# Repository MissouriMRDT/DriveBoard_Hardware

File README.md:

# DriveBoard_Hardware
Hardware files for Drive Board

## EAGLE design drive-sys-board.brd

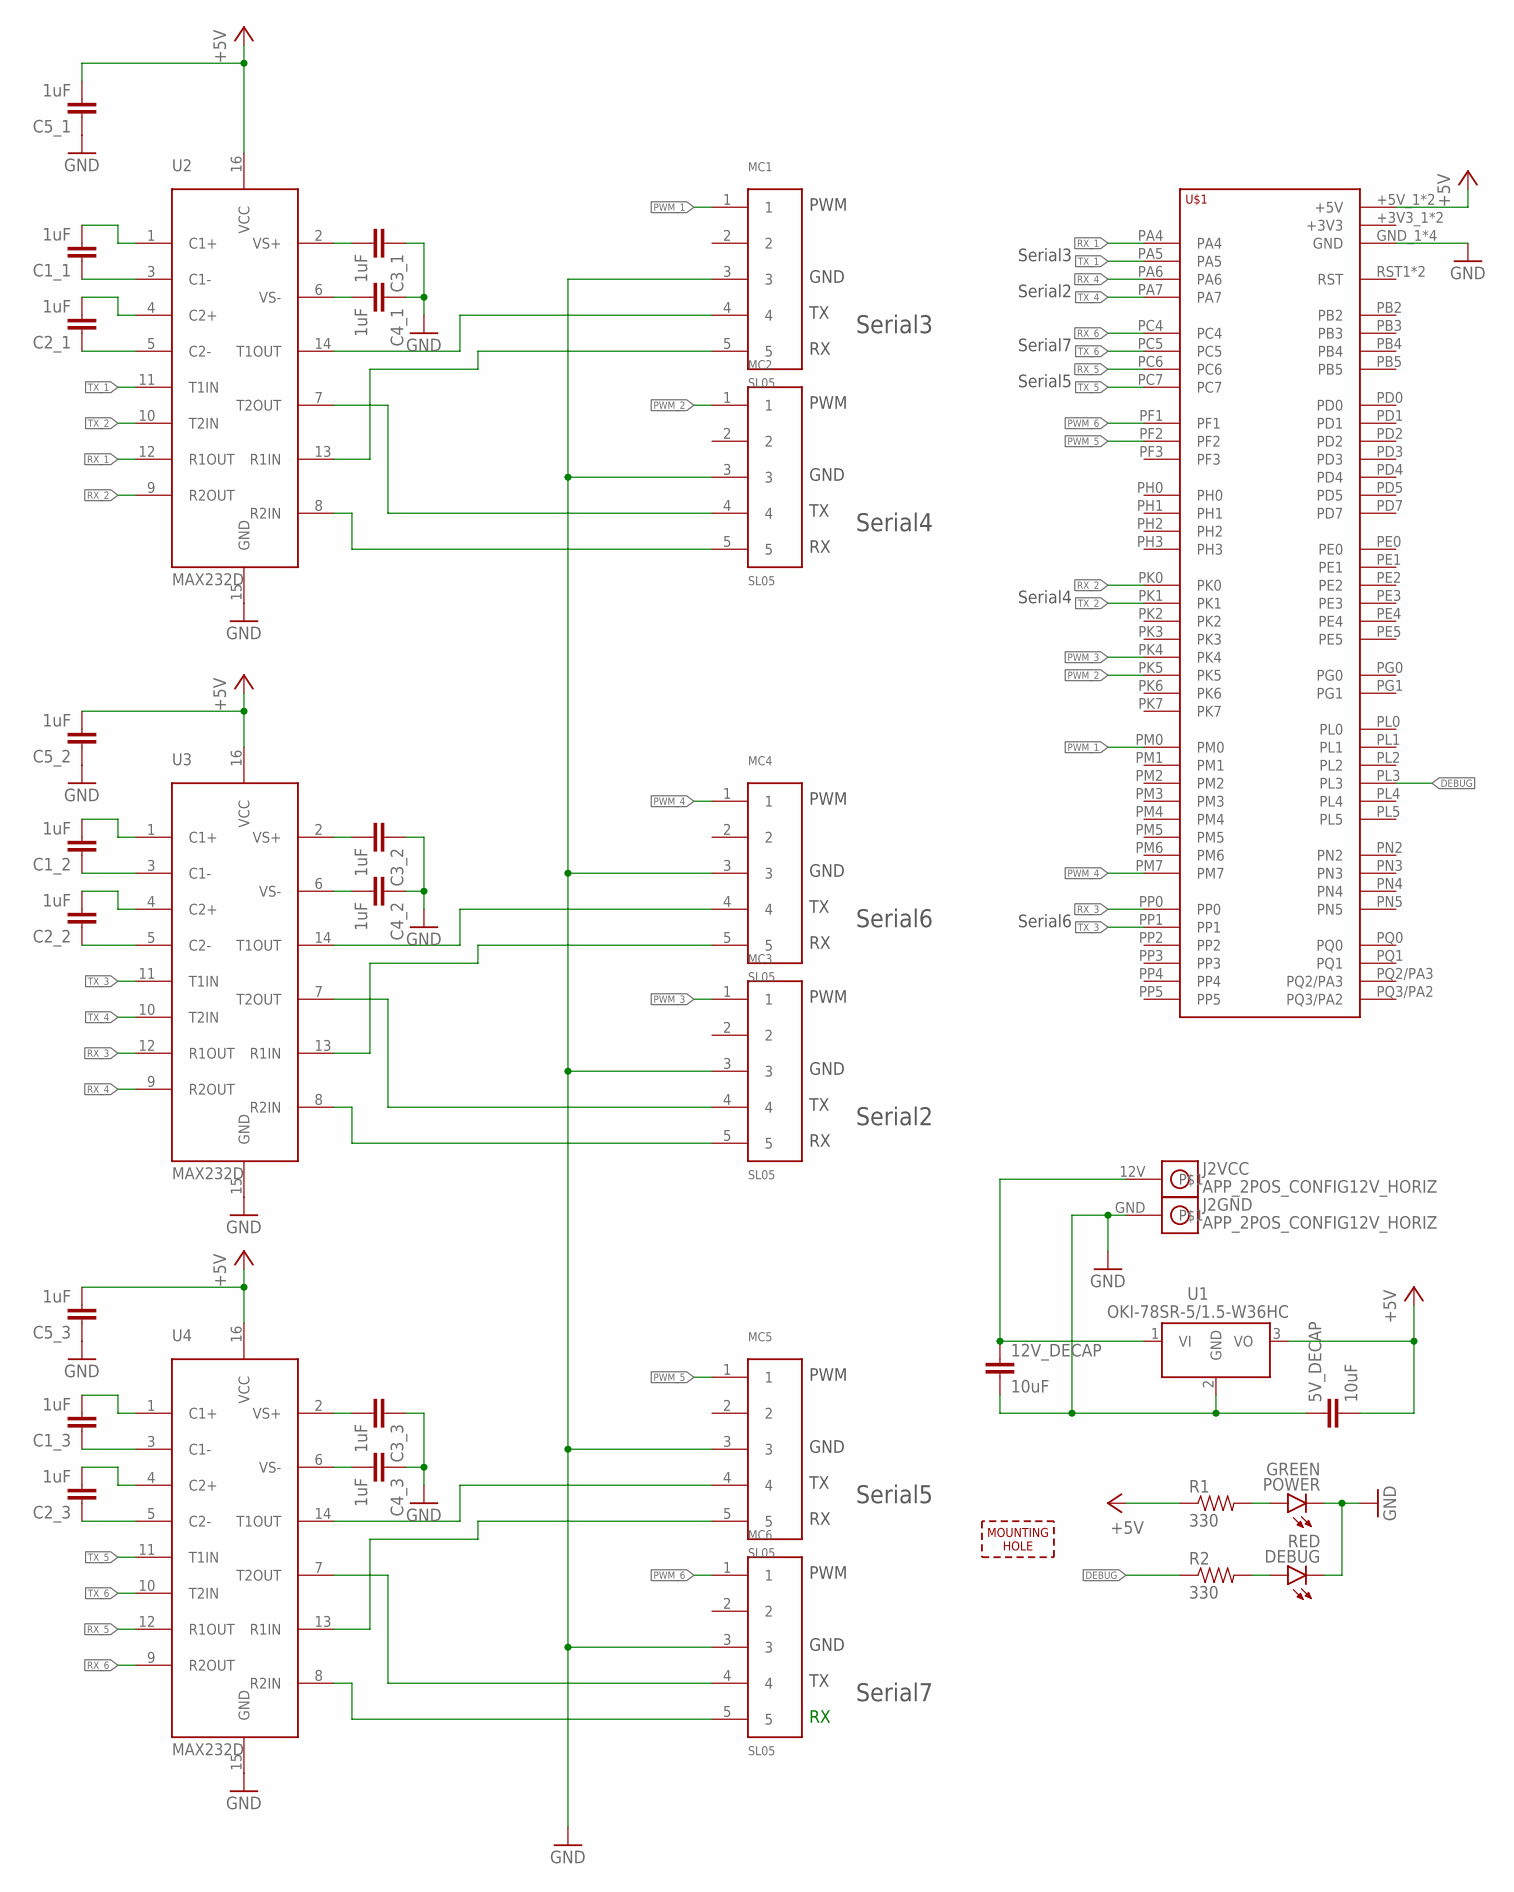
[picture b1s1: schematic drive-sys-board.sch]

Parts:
5V_DECAP, 12V_DECAP: 10uF; 0805
C1_1, C1_2, C1_3, C2_1, C2_2, C2_3, C3_1, C3_2, C3_3, C4_1, C4_2, C4_3, C5_1, C5_2, C5_3: 1uF; 0805
DEBUG: RED; LED-1206
H2: MOUNTING_HOLE#6; #6_SCREW
J2: APP_2POS_CONFIG12V_HORIZ; APP45_12V_HORIZ_CONFIG
MC1, MC2, MC3, MC4, MC5, MC6: SL05; MOLEX_SL_05_TH
POWER: GREEN; LED-1206
R1, R2: 330; 0805
U1: OKI-78SR-5/1.5-W36HC; OKI-78SR_HORIZ
U2, U3, U4: MAX232D; SOIC16
U$1: TIVA-1294; TIVA-C-CONNECTED

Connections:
+5V: 5V_DECAP.2, C5_1.2, C5_2.2, C5_3.2, R1.1, U1.3 (VO), U2.16 (VCC), U3.16 (VCC), U4.16 (VCC), U$1.+5V_1 (+5V), U$1.+5V_2 (+5V)
DEBUG: R2.1, U$1.PL3
GND: 5V_DECAP.1, 12V_DECAP.2, C3_1.1, C3_2.1, C3_3.1, C4_1.1, C4_2.1, C4_3.1, C5_1.1, C5_2.1, C5_3.1, DEBUG.C, J2.GND, MC1.3, MC2.3, MC3.3, MC4.3, MC5.3, MC6.3, POWER.C, U1.2 (GND), U2.15 (GND), U3.15 (GND), U4.15 (GND), U$1.GND_1 (GND), U$1.GND_2 (GND), U$1.GND_3 (GND), U$1.GND_4 (GND)
unnamed: C1_1.2, U2.1 (C1+)
unnamed: C1_1.1, U2.3 (C1-)
unnamed: 12V_DECAP.1, J2.12V, U1.1 (VI)
unnamed: C2_1.2, U2.4 (C2+)
unnamed: C2_1.1, U2.5 (C2-)
unnamed: C3_1.2, U2.2 (VS+)
unnamed: C4_1.2, U2.6 (VS-)
unnamed: DEBUG.A, R2.2
unnamed: C1_2.2, U3.1 (C1+)
unnamed: C1_2.1, U3.3 (C1-)
unnamed: C2_2.2, U3.4 (C2+)
unnamed: C3_2.2, U3.2 (VS+)
unnamed: C4_2.2, U3.6 (VS-)
unnamed: C2_2.1, U3.5 (C2-)
unnamed: POWER.A, R1.2
unnamed: C1_3.2, U4.1 (C1+)
unnamed: C1_3.1, U4.3 (C1-)
unnamed: C2_3.2, U4.4 (C2+)
unnamed: C3_3.2, U4.2 (VS+)
unnamed: C4_3.2, U4.6 (VS-)
unnamed: C2_3.1, U4.5 (C2-)
unnamed: MC5.4, U4.14 (T1OUT)
unnamed: MC6.5, U4.8 (R2IN)
unnamed: MC6.4, U4.7 (T2OUT)
unnamed: MC5.5, U4.13 (R1IN)
unnamed: MC3.5, U3.8 (R2IN)
unnamed: MC3.4, U3.7 (T2OUT)
unnamed: MC4.4, U3.14 (T1OUT)
unnamed: MC4.5, U3.13 (R1IN)
unnamed: MC2.5, U2.8 (R2IN)
unnamed: MC2.4, U2.7 (T2OUT)
unnamed: MC1.4, U2.14 (T1OUT)
unnamed: MC1.5, U2.13 (R1IN)
PWM_1: MC1.1, U$1.PM0
PWM_2: MC2.1, U$1.PK5
PWM_3: MC3.1, U$1.PK4
PWM_4: MC4.1, U$1.PM7
PWM_5: MC5.1, U$1.PF2
PWM_6: MC6.1, U$1.PF1
RX_1: U2.12 (R1OUT), U$1.PA4
RX_2: U2.9 (R2OUT), U$1.PK0
RX_3: U3.12 (R1OUT), U$1.PP0
RX_4: U3.9 (R2OUT), U$1.PA6
RX_5: U4.12 (R1OUT), U$1.PC6
RX_6: U4.9 (R2OUT), U$1.PC4
TX_1: U2.11 (T1IN), U$1.PA5
TX_2: U2.10 (T2IN), U$1.PK1
TX_3: U3.11 (T1IN), U$1.PP1
TX_4: U3.10 (T2IN), U$1.PA7
TX_5: U4.11 (T1IN), U$1.PC7
TX_6: U4.10 (T2IN), U$1.PC5

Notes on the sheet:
PWM
GND
Serial2
Serial3
Serial7
Serial5
Serial4
Serial6

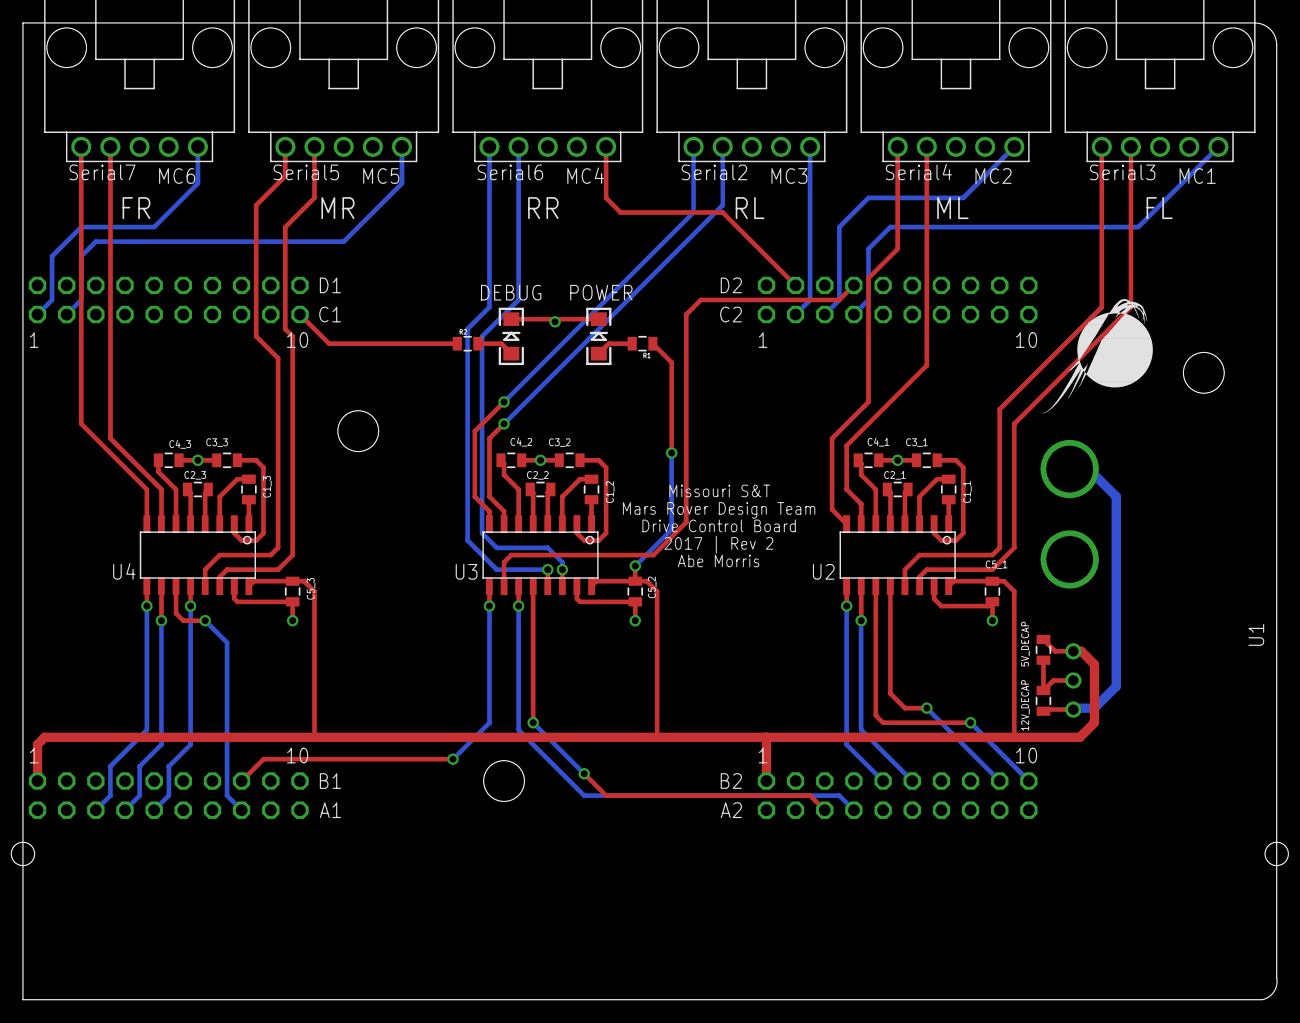
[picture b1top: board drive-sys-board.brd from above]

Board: 2 copper layers, 109.2 x 85.1 mm, 37 parts (0 on the bottom side), 54 nets.

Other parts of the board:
H1, H3: MOUNTING_HOLE#6; #6_SCREW
U$2: MRDT_LOGO

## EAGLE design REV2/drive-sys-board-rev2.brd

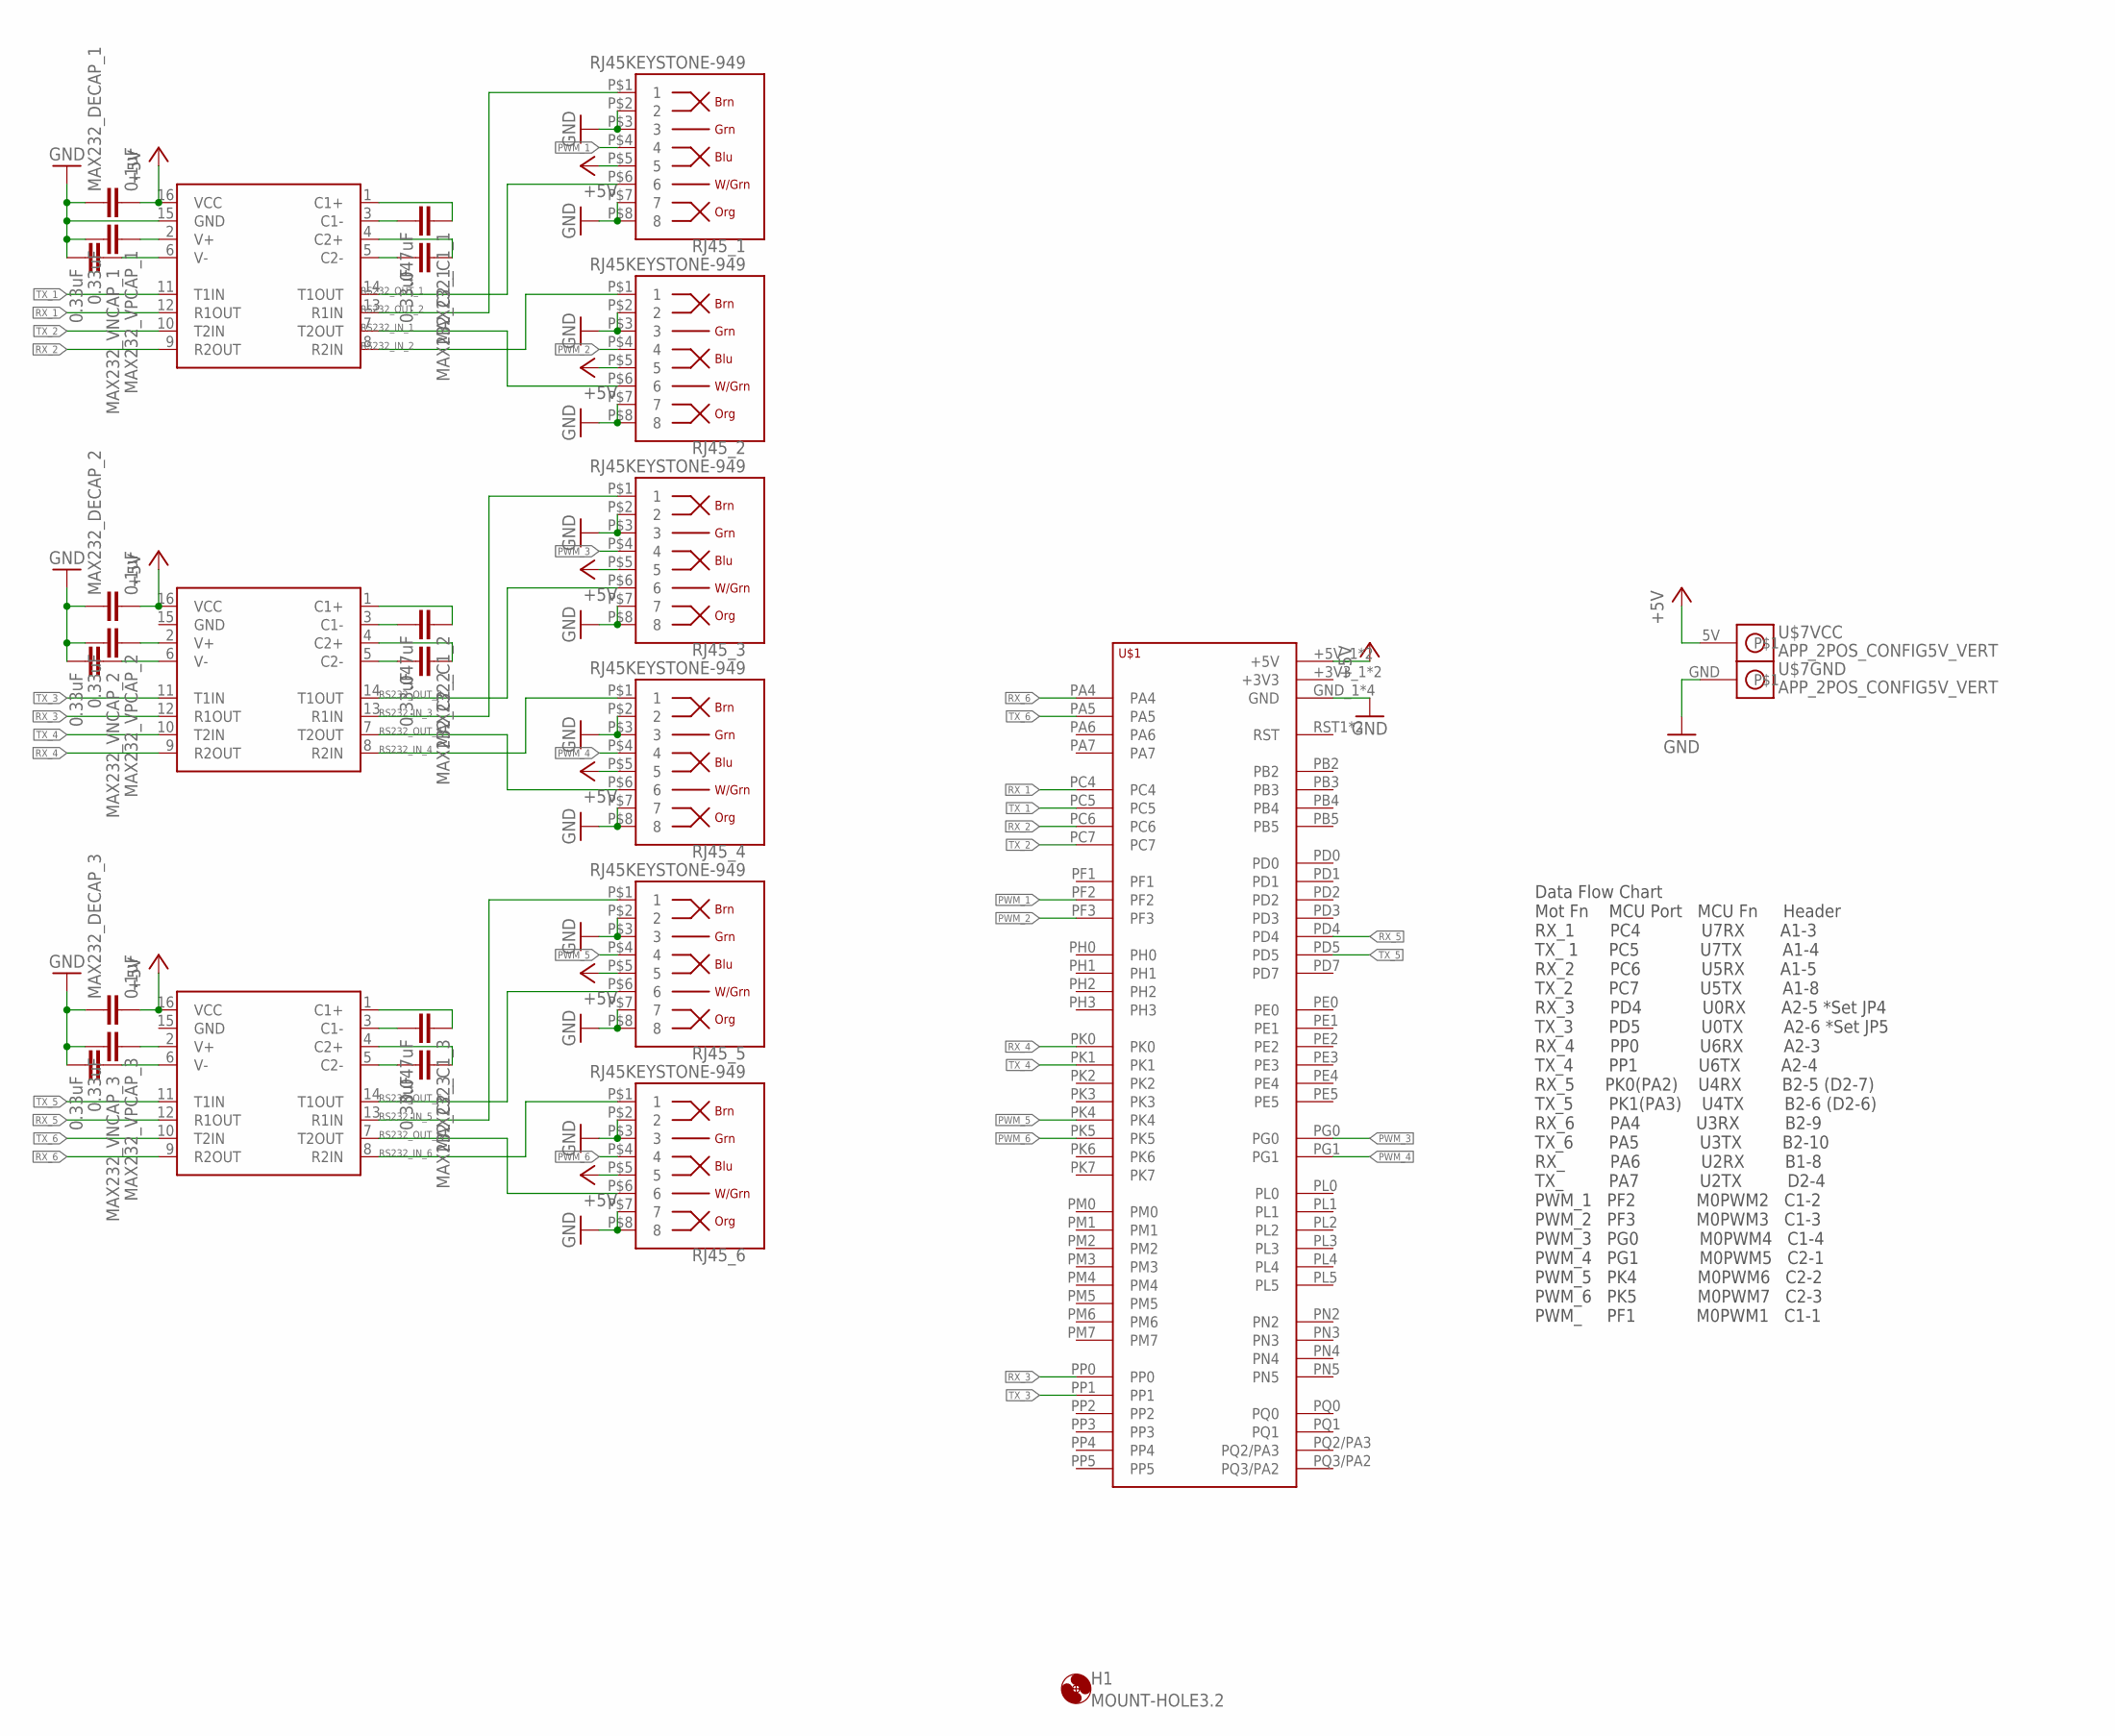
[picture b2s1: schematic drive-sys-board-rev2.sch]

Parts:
H1: MOUNT-HOLE3.2; 3,2
MAX232_1, MAX232_2, MAX232_3: MAX3232SO16; SO16
MAX232_C1_1, MAX232_C1_2: .047uF; 1206
MAX232_C1_3: 0.047uF; 1206
MAX232_C2_1, MAX232_C2_2, MAX232_C2_3, MAX232_VNCAP_1, MAX232_VNCAP_2, MAX232_VNCAP_3, MAX232_VPCAP_1, MAX232_VPCAP_2, MAX232_VPCAP_3: 0.33uF; 1206
MAX232_DECAP_1, MAX232_DECAP_2, MAX232_DECAP_3: 0.1uF; 1206
RJ45_1, RJ45_2, RJ45_3, RJ45_4, RJ45_5, RJ45_6: RJ45KEYSTONE-949; KEYSTONE-949
U$1: TIVA-C-CONNECTED
U$7: APP_2POS_CONFIG5V_VERT; APP45_5V_VERT_CONFIG

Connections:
+5V: MAX232_1.16 (VCC), MAX232_2.16 (VCC), MAX232_3.16 (VCC), MAX232_DECAP_1.2, MAX232_DECAP_2.2, MAX232_DECAP_3.2, RJ45_1.P$5 (5), RJ45_2.P$5 (5), RJ45_3.P$5 (5), RJ45_4.P$5 (5), RJ45_5.P$5 (5), RJ45_6.P$5 (5), U$1.+5V_1 (+5V), U$1.+5V_2 (+5V), U$7.5V
GND: MAX232_1.15 (GND), MAX232_DECAP_1.1, MAX232_DECAP_2.1, MAX232_DECAP_3.1, MAX232_VNCAP_1.2, MAX232_VNCAP_2.2, MAX232_VNCAP_3.2, MAX232_VPCAP_1.2, MAX232_VPCAP_2.2, MAX232_VPCAP_3.2, RJ45_1.P$2 (2), RJ45_1.P$3 (3), RJ45_1.P$7 (7), RJ45_1.P$8 (8), RJ45_2.P$2 (2), RJ45_2.P$3 (3), RJ45_2.P$7 (7), RJ45_2.P$8 (8), RJ45_3.P$2 (2), RJ45_3.P$3 (3), RJ45_3.P$7 (7), RJ45_3.P$8 (8), RJ45_4.P$2 (2), RJ45_4.P$3 (3), RJ45_4.P$7 (7), RJ45_4.P$8 (8), RJ45_5.P$2 (2), RJ45_5.P$3 (3), RJ45_5.P$7 (7), RJ45_5.P$8 (8), RJ45_6.P$2 (2), RJ45_6.P$3 (3), RJ45_6.P$7 (7), RJ45_6.P$8 (8), U$1.GND_1 (GND), U$1.GND_2 (GND), U$1.GND_3 (GND), U$1.GND_4 (GND), U$7.GND
unnamed: MAX232_1.1 (C1+), MAX232_C1_1.1
unnamed: MAX232_2.1 (C1+), MAX232_C1_2.1
unnamed: MAX232_3.1 (C1+), MAX232_C1_3.1
unnamed: MAX232_1.2 (V+), MAX232_VPCAP_1.1
unnamed: MAX232_2.2 (V+), MAX232_VPCAP_2.1
unnamed: MAX232_3.2 (V+), MAX232_VPCAP_3.1
unnamed: MAX232_1.3 (C1-), MAX232_C1_1.2
unnamed: MAX232_2.3 (C1-), MAX232_C1_2.2
unnamed: MAX232_3.3 (C1-), MAX232_C1_3.2
unnamed: MAX232_1.4 (C2+), MAX232_C2_1.1
unnamed: MAX232_2.4 (C2+), MAX232_C2_2.1
unnamed: MAX232_3.4 (C2+), MAX232_C2_3.1
unnamed: MAX232_1.5 (C2-), MAX232_C2_1.2
unnamed: MAX232_2.5 (C2-), MAX232_C2_2.2
unnamed: MAX232_3.5 (C2-), MAX232_C2_3.2
unnamed: MAX232_1.6 (V-), MAX232_VNCAP_1.1
unnamed: MAX232_2.6 (V-), MAX232_VNCAP_2.1
unnamed: MAX232_3.6 (V-), MAX232_VNCAP_3.1
PWM_1: RJ45_1.P$4 (4), U$1.PF2
PWM_2: RJ45_2.P$4 (4), U$1.PF3
PWM_3: RJ45_3.P$4 (4), U$1.PG0
PWM_4: RJ45_4.P$4 (4), U$1.PG1
PWM_5: RJ45_5.P$4 (4), U$1.PK4
PWM_6: RJ45_6.P$4 (4), U$1.PK5
RS232_IN_1: MAX232_1.13 (R1IN), RJ45_1.P$1 (1)
RS232_IN_2: MAX232_1.8 (R2IN), RJ45_2.P$1 (1)
RS232_IN_3: MAX232_2.13 (R1IN), RJ45_3.P$1 (1)
RS232_IN_4: MAX232_2.8 (R2IN), RJ45_4.P$1 (1)
RS232_IN_5: MAX232_3.13 (R1IN), RJ45_5.P$1 (1)
RS232_IN_6: MAX232_3.8 (R2IN), RJ45_6.P$1 (1)
RS232_OUT_1: MAX232_1.14 (T1OUT), RJ45_1.P$6 (6)
RS232_OUT_2: MAX232_1.7 (T2OUT), RJ45_2.P$6 (6)
RS232_OUT_3: MAX232_2.14 (T1OUT), RJ45_3.P$6 (6)
RS232_OUT_4: MAX232_2.7 (T2OUT), RJ45_4.P$6 (6)
RS232_OUT_5: MAX232_3.14 (T1OUT), RJ45_5.P$6 (6)
RS232_OUT_6: MAX232_3.7 (T2OUT), RJ45_6.P$6 (6)
RX_1: MAX232_1.12 (R1OUT), U$1.PC4
RX_2: MAX232_1.9 (R2OUT), U$1.PC6
RX_3: MAX232_2.12 (R1OUT), U$1.PP0
RX_4: MAX232_2.9 (R2OUT), U$1.PK0
RX_5: MAX232_3.12 (R1OUT), U$1.PD4
RX_6: MAX232_3.9 (R2OUT), U$1.PA4
TX_1: MAX232_1.11 (T1IN), U$1.PC5
TX_2: MAX232_1.10 (T2IN), U$1.PC7
TX_3: MAX232_2.11 (T1IN), U$1.PP1
TX_4: MAX232_2.10 (T2IN), U$1.PK1
TX_5: MAX232_3.11 (T1IN), U$1.PD5
TX_6: MAX232_3.10 (T2IN), U$1.PA5

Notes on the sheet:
Data Flow Chart Mot Fn MCU Port MCU Fn Header RX_1 PC4 U7RX A1-3 TX_ 1 PC5 U7TX A1-4 RX_2 PC6 U5RX A1-5 TX_2 PC7 U5TX A1-8 RX_3 PD4 U0RX A2-5 *Set JP4 TX_3 PD5 U0TX A2-6 *Set JP5 RX_4 PP0 U6RX A2-3 TX_4 PP1 U6TX A2-4 RX_5 PK0(PA2) U4RX B2-5 (D2-7) TX_5 PK1(PA3) U4TX B2-6 (D2-6) RX_6 PA4 U3RX B2-9 T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

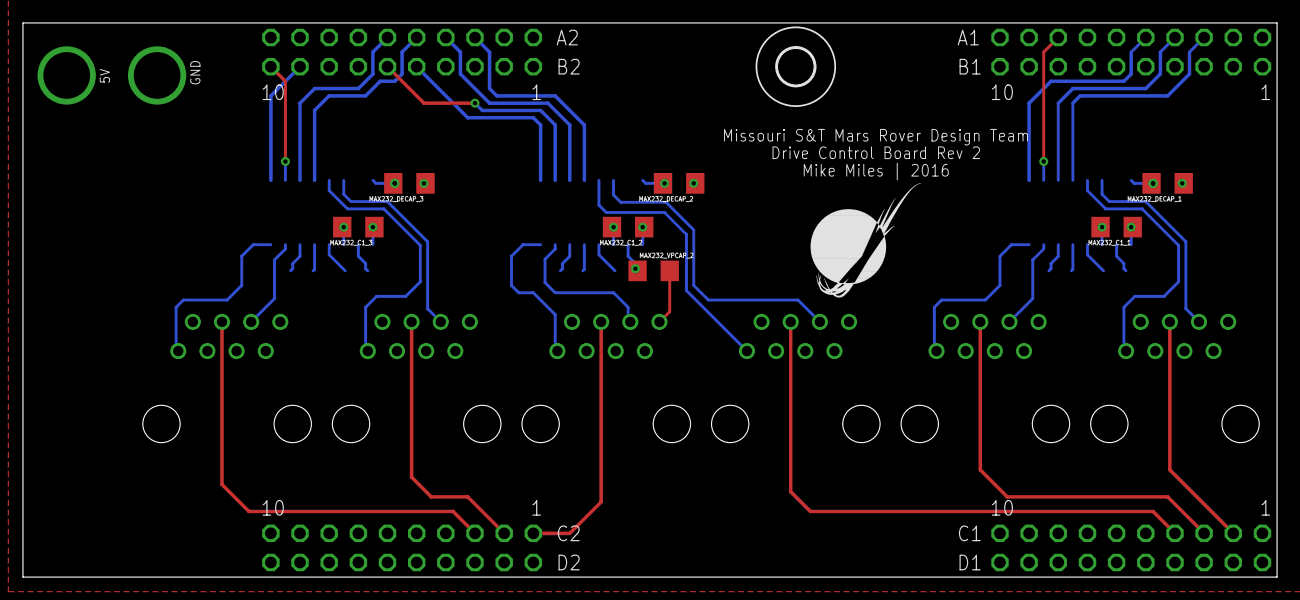
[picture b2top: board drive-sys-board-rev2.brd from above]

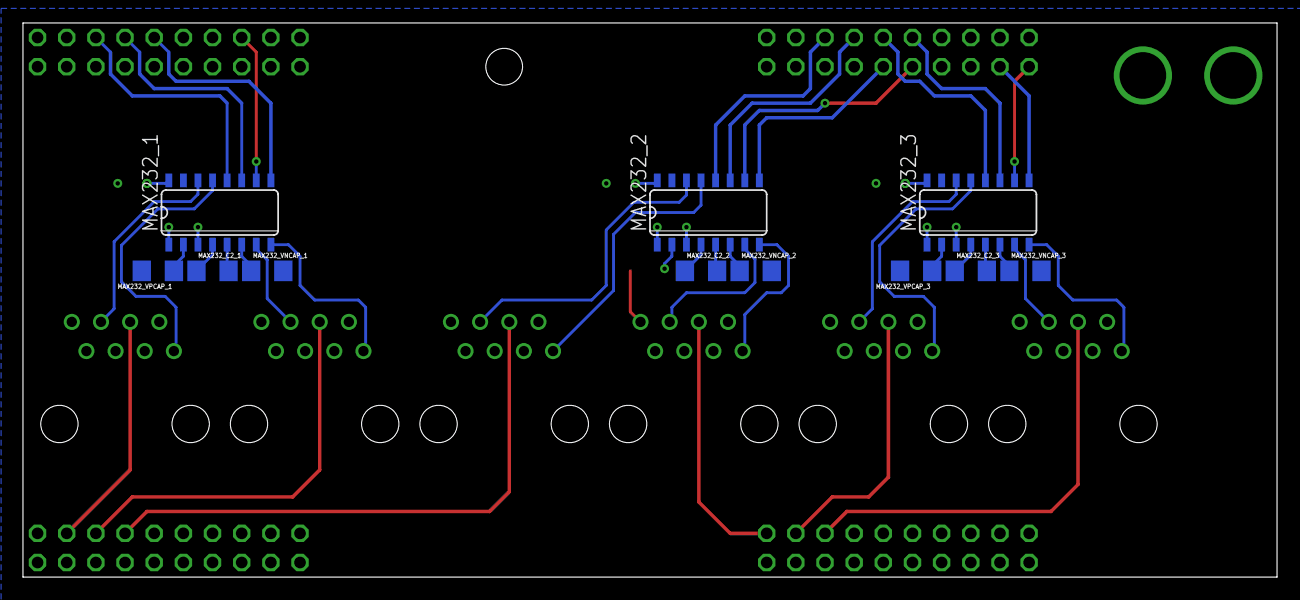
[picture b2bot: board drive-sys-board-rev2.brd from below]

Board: 2 copper layers, 109.2 x 48.3 mm, 28 parts (11 on the bottom side), 50 nets.

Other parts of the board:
U$2: MRDT_LOGO

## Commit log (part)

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2015-11-12 added .gitignore
    copied from RoboticArm-Hardware
2015-11-13 created schematic, started board placement and routing
2015-11-13 i think i'm finished with rev 1. Finished placement and routing.
    Placed MAX3077, res's, caps, and rj45's for each motor. Routed all
    power, pwm, and uarts.
2015-11-13 updated library to reflect movement of tiva header pin number labels
2015-11-14 REV 1 FINAL VERSION
    This is the final version of rev 1, however, after a talk with Ethan
    Wilhelm, the form factor does not best match that desired for
    integration into the frame. This version also did not allow mounting due
    to spacing above the 1294's RJ45 jack.
2015-11-15 Finished REV 2?
    I just power through and finished rev 2 I think..
2015-11-17 added hole device, removed unnecessary hole layers
2016-01-11 swapped power input conn from screw terminal to molex 3pin
2016-01-11 repositioned logo
2016-01-11 swapped max3077 component for same in diff lib, changed some lib parts and updated
2016-01-12 changed rj45 conn
2016-01-12 finalized board
2016-01-12 added gerbers
2016-01-20 finished rs232 drive board
2016-01-20 okay nvm not finalized... almost used a IEA232 xcvr... need to use the added rs232 xcvr
2016-01-21 final rs232 version
2016-01-21 changed traces to 12 mil, need to check out L-reconfig before ordering
2016-02-01 fixed wrong width on segment of wire - need to update APP and send off!
2016-02-01 reorganized, need to add in rev1 from older branch
2016-02-02 adjusted board dims, regen'ed gerbers
2016-03-18 updated roboteq profiles
    Both SBL1360s and MBL1660s take the master_clspd profile. Be sure to
    ensure the right polarity of the Number of Poles parameter - it varies
    for each motor.
2016-10-11 Replaced RJ45 Connectors with 15-Pin D-Subs
2016-10-21 Updated connectors and UART hardware
    - Replaced DSubs with Molex-SL 5-pin Connectors
    - Swapped MAX3232 for MAX3078
2016-10-22 Deleted unnecessary folders within the repository
    - Deleted a temp folder made to store exported parts that were not yet
    in the EAGLE-Libraries-Hardware repository
    - Deleted "moco_profiles" folder since it applied to the previous motor
    controllers.
2016-10-23 Changed named wire for 3V3 to supply symbol
2016-10-23 Switched vertical power connector for horizontal.
    APP45_12V_VERT_CONFIG switched to APP45_12V_HORIZ_CONFIG
2016-10-27 Updated board label
    Added my name and the year
2016-10-27 updated gitignore for newer versions of Eagle and removed unnecessary files
2016-10-28 Made slight changes to prepare for board review
    - Added decoupling capacitors to OKI
    - Replaced VCC supply symbol with +5V
    - Disconnected +5V from capacitors (let them connect to +5V plane)
    - Swap connectors 3 and 4 to create progression from right to left
2016-11-07 Flipped the silkscreen for the 5Pin SLs
2016-11-07 Adjusted positions of several board components
    - Repositioned OKI to allow for more room
    - Shifted the two leftmost MAX232s to the left
    - Shifted SL Connectors to be evenly spaced between MAX232s
2016-11-07 Moved silkscreen labels
2016-12-12 Changed serial pairs to match Tiva hardware
2016-12-13 Fixed RS232 chip capacitors
    Several capacitors were going to Vcc when they should have been going to
    Gnd
2016-12-13 Began routing traces
2017-01-31 Routed PWM traces and added power indicator led
2017-01-31 Prep for Board Review
    - Labeled schematic with corresponding Serial channels (from hardware
    serial on Tiva.
    - Added Power Indicator LED and Debug LED
    - Still need to decide on current limiting resistors for LEDs
2017-02-02 Adjusted labels and removed top +5V plane
2017-02-02 Finished routing
2017-02-04 Changes from 2nd Review
    - changed led direction
    - changes led schematic
    - moved vias above max232
    - thickened 12v line
2017-11-10 Modified 2017 Drive Board for BOD 2018
    -Switched all vertical SL connectors to horizontal connectors.
    -Moved horizontal connectors to top of board so that there are only
    connectors on the top and right side of the board.
    -Extended the bottom of the board out further by ~0.6 inches in order to
    place .08 inch diameter mounting holes.
    -Moved ICs and other passives connected to vertical SL connectors
2018-03-26 Created new project in KiCad
    Designing Drive Board Rev.2 2018 in KiCad. Farewell EAGLE.
2018-03-26 Added Power Circuitry in Schematic
2018-03-26 Drive Serial Added
2018-03-26 Added Servos
2018-04-09 Schematic complete and txt file added
2018-04-13 Created full board
2018-04-16 Finished Board Layout
2018-05-03 Fixed Tiva Footprint
2018-05-13 changed header footprint from 1.27mm to 2.54mm
2018-10-13 Cleared Repo
2018-10-16 Cleaned up, organized, and labeled schematic components
2018-10-20 Assigned packages and created layout
2018-10-21 Made pcb layout
2018-10-23 Updated silkscreens
2018-10-25 Revised molex pins and created pin layout and connections txt files
2018-10-25 Revised and organized txt documentation files
2018-11-03 Added traces to pcb layout
2018-11-11 Updated some connections
2018-11-11 Updated molex pins
2018-11-29 Changing to AP1509
2018-11-30 Updated schematic
2018-12-02 First board review revisions txt file
2018-12-04 Updated to using buttons/switch
2018-12-14 changes to schematic and starting changes to layout
2018-12-15 making changes
2018-12-15 finishing changes
2018-12-16 changed BOM
2018-12-16 updating changes (Rev1 Review)
2018-12-16 Updated board review revision progress
2019-03-03 Created rev 2
2019-03-03 Finished BOM
2019-03-03 board review
2019-09-30 begin rough schematic
2019-10-05 Update DriveBoard2020.sch-bak
2019-10-05 Tiva, level shifters, molex
    This reverts commit 14c33bf3896d072e8babb810b236ce765600d1b4.
2019-10-05 organized schematic
2019-10-05 added LED's
2019-10-05 Switches and buttons, forwarded to TIVA
2019-10-07 started assigning footprints
2019-10-07 added capacitors to level shifters, added oki for 5v, finished assigning footprints
2019-10-08 started layout
2019-10-09 fixing bullshit
2019-10-09 tweaked layout
2019-10-09 worked really hard on making layout pretty
2019-11-11 switch level shifters to 3232's
2019-11-15 Added lighting stuff
2019-11-15 assigned some footprints
2019-11-17 worked on integrating lighting and drive board schematic
2019-11-18 minor changes to layout
2019-11-18 working on layout
2019-11-18 finished placing components on layout
2019-11-19 cleaned up repo
2019-11-19 cleaned up schematic some
2019-11-20 edge cuts
2019-11-22 generated step files
2019-12-03 Worked on grids
2019-12-09 added serials and relabled for individual wheel control
2019-12-09 added capacitors to OKI's
2019-12-09 added new switches and indicators
2019-12-09 assigned footprints
2019-12-12 finished schematic
2019-12-12 layout progress
2019-12-12 working on traces
2019-12-12 traces complete
2019-12-12 edgecuts, signatures
2019-12-12 fixed LED and renamed silkscreens
2019-12-12 generated gerbs and step files
2019-12-13 Changes from Review
2019-12-17 re-placed footprints on layout
2019-12-17 more layout changes
2019-12-20 silkscreens and via stitching, corrected some awful traces
2019-12-20 corrected a few more traces
2019-12-21 moved some labels on schematic and redid BOM
2020-01-04 just kidding just a few more things to save from layout
2020-01-07 Fixed gerbs files
2020-01-09 updated pin layout document
2020-09-12 Repo Reorganization
2020-09-14 Added Tiva and Power Connections
2020-09-20 Added Molex connectors, added all serial connections, added LED indicators
2020-09-26 ODrive PWR terminal added
2020-09-26 Added CAN Controller and Transceiver
    Need to verify 16Mhz is correct oscillator for use. Must be parallel cut crystall.
2020-09-26 Fixing CAN Hookup with Transceiver
2020-10-01 Added ODrive Serial, Added LED Indicators, Changed Serial Naming
    Changed serial naming for easier understanding of pinout. Added LED indicators for 5V line, CAN serial, and both ODrive serial connections.
2020-10-05 Absolute Encoder Connections Added
2020-10-08 Added ODrive Data Connectors, Switched schematic page size, removed 12 Logic bus
2020-10-11 Updated LEDs, Organized file layout, removed old files
2020-11-09 Added Footprint for all Components, started board
    Switched ferrite beads to fuses
2020-11-09 Added 12V logic line
2020-11-10 Odrive Pads Updated, Board Outline Finished, Andersons added to board
    12VA pin on anderson symbol was re-assigned to work on pad 2 for 2 port anderson connector.
2020-11-14 All Major Components footprints placed.
    Remaining are resistors, capacitors, and inductors. Silkscreen is also required.
2020-11-15 Added traces for buttons, and moved most resistors and LEDs into position
2020-11-15 All Components in Place. Small amounts of trace work remaining.
2020-11-15 All Components and Traces Placed. Silkscreen Updated.
2020-11-16 Changed Actuation trace width. Added gerbs and BOM to documentation. Added TIVA connections and board connectors text files.
2020-11-17 Switched TIVA SMD bottom to THT. Moved Odrive Andersons and re-traced pwr. Added names to LEDs.
2020-11-23 All Components and Traces Placed
    Finished updating schematic to meet CDR changes.
2020-11-29 Added Gerbs and BOM
2020-11-30 Changed Top plane to GND and routed 3V3 traces.
    Should fix GND islands.
2020-11-30 STEP file fixed, Gerbs Updated, BOM Finished
2020-11-30 Added Digikey Part Number
2020-11-30 gerbs moved to .zip file
2021-09-21 I deleted some 2021 things
2021-09-21 3V3Oki, Tiva, Power LED
2021-09-24 Basically Finished
2021-09-24 I did something guys
2021-09-24 Added Fault LEDs, and Adjusted Placement
2021-09-24 Microfit YASSS~
2021-09-27 Organization for BoardA
2021-10-06 Added 5V OKI, Level Shifters, Organization
2021-10-13 Removed Encoder, Fixed Resistor Values
2021-10-13 Added VESC Connectors, Fixed Switch Resistors
2021-10-21 Changed Switches Back to Buttons; Created Schematic PDF
2021-11-08 6-Pin Molex and Layour from B
2021-11-08 Fix Mislabeled Serial Connections, Serial Traces, GND Vias
2021-11-16 CDR Changes
2021-11-18 Added CDR Alumni Notes
2021-12-08 .STEP file moved to documentation folder
2022-02-20 Finished Schematic and Layout
2022-02-20 Fixed Ethernet Port
2022-02-20 removed the .net exclusion from the gitignore
2022-02-20 Made Traces "Not Ugly"
2022-02-21 BIG Labels
2022-02-22 Board Review Changes
2022-03-10 Changed Buck Converter; Redid Gerbs
2022-03-14 zipped together gerber files
2022-09-15 Driveboard 2023
    New Branch of Driveboard
2022-09-15 Driveboard Rev1 Start
    Teensy, Connectors, Anderson added
2022-09-24 Slight Schematic Change
    Changed the schematic slightly so it wouldn't look too cluttered
2022-09-24 Fixed Changes
    Changed 12V to 36V, same thing with OKI from TSR
    Changed switch to a 2 position switch
    Changed 12V LED to 36V and add 3k Resistor
    Changed all Rx LED to Yellow
2022-09-24 Microfit to SL
    Changed microfits to SL
2022-09-30 Documentation
    Schematic PDF
2022-10-04 Assigned Footprints
    Assigned footprints
2022-10-29 PCB Layout
    Started and Finished Rev1 of DriveBoard
2022-11-03 Layout Review Board
    Finished Changes. Needs to add signatures.
2022-11-03 Added Signature
    Signature added, still need other signatures
2022-11-09 Fixed 1 and 2 Problems from LR
    Increased size of Ground Planes & Ran Traces Away from Ground (Maybe not complete)
2022-11-19 Signature adding and typo correction
    Added my signature and corrected a typo on the board
2022-11-19 Himanth Bobba Signature Added
2022-11-19 Cleaned up board
    Corrected a typo and aligned some texts boxes
2023-03-05 Rev2 Drive Board
    Started Rev2 of Drive Board. Combined Drive Board, Multimedia Board, and Gimbal Board all in one.
2023-03-08 Schematic Review
    Updated connectors, power, notations, pin assignments, and started to construct an Encoder for buttons
2023-03-10 PCB Layout
    Updated the footnotes.
    Started and almost finished the layout.
    Still needs buttons and encoder.
2023-03-15 Added Signature
2023-03-19 Core Board PCB
    Finished Core Board PCB
2023-03-19 Core Board PCB
    Layout Finished
2023-03-19 Core Board PCB
2023-03-21 PCB Layout Core Board
    Finished
2023-03-21 Corrected Capacitor
2023-03-21 generated gerbs and fixed files
2023-04-19 Fixed CoreBoard PCB
    Fixed Pin Assignments

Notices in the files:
parts and their libraries:
SparkFun-Capacitors: Licensing: Creative Commons ShareAlike 4.0 International - https://creativecommons.org/licenses/by-sa/4.0
